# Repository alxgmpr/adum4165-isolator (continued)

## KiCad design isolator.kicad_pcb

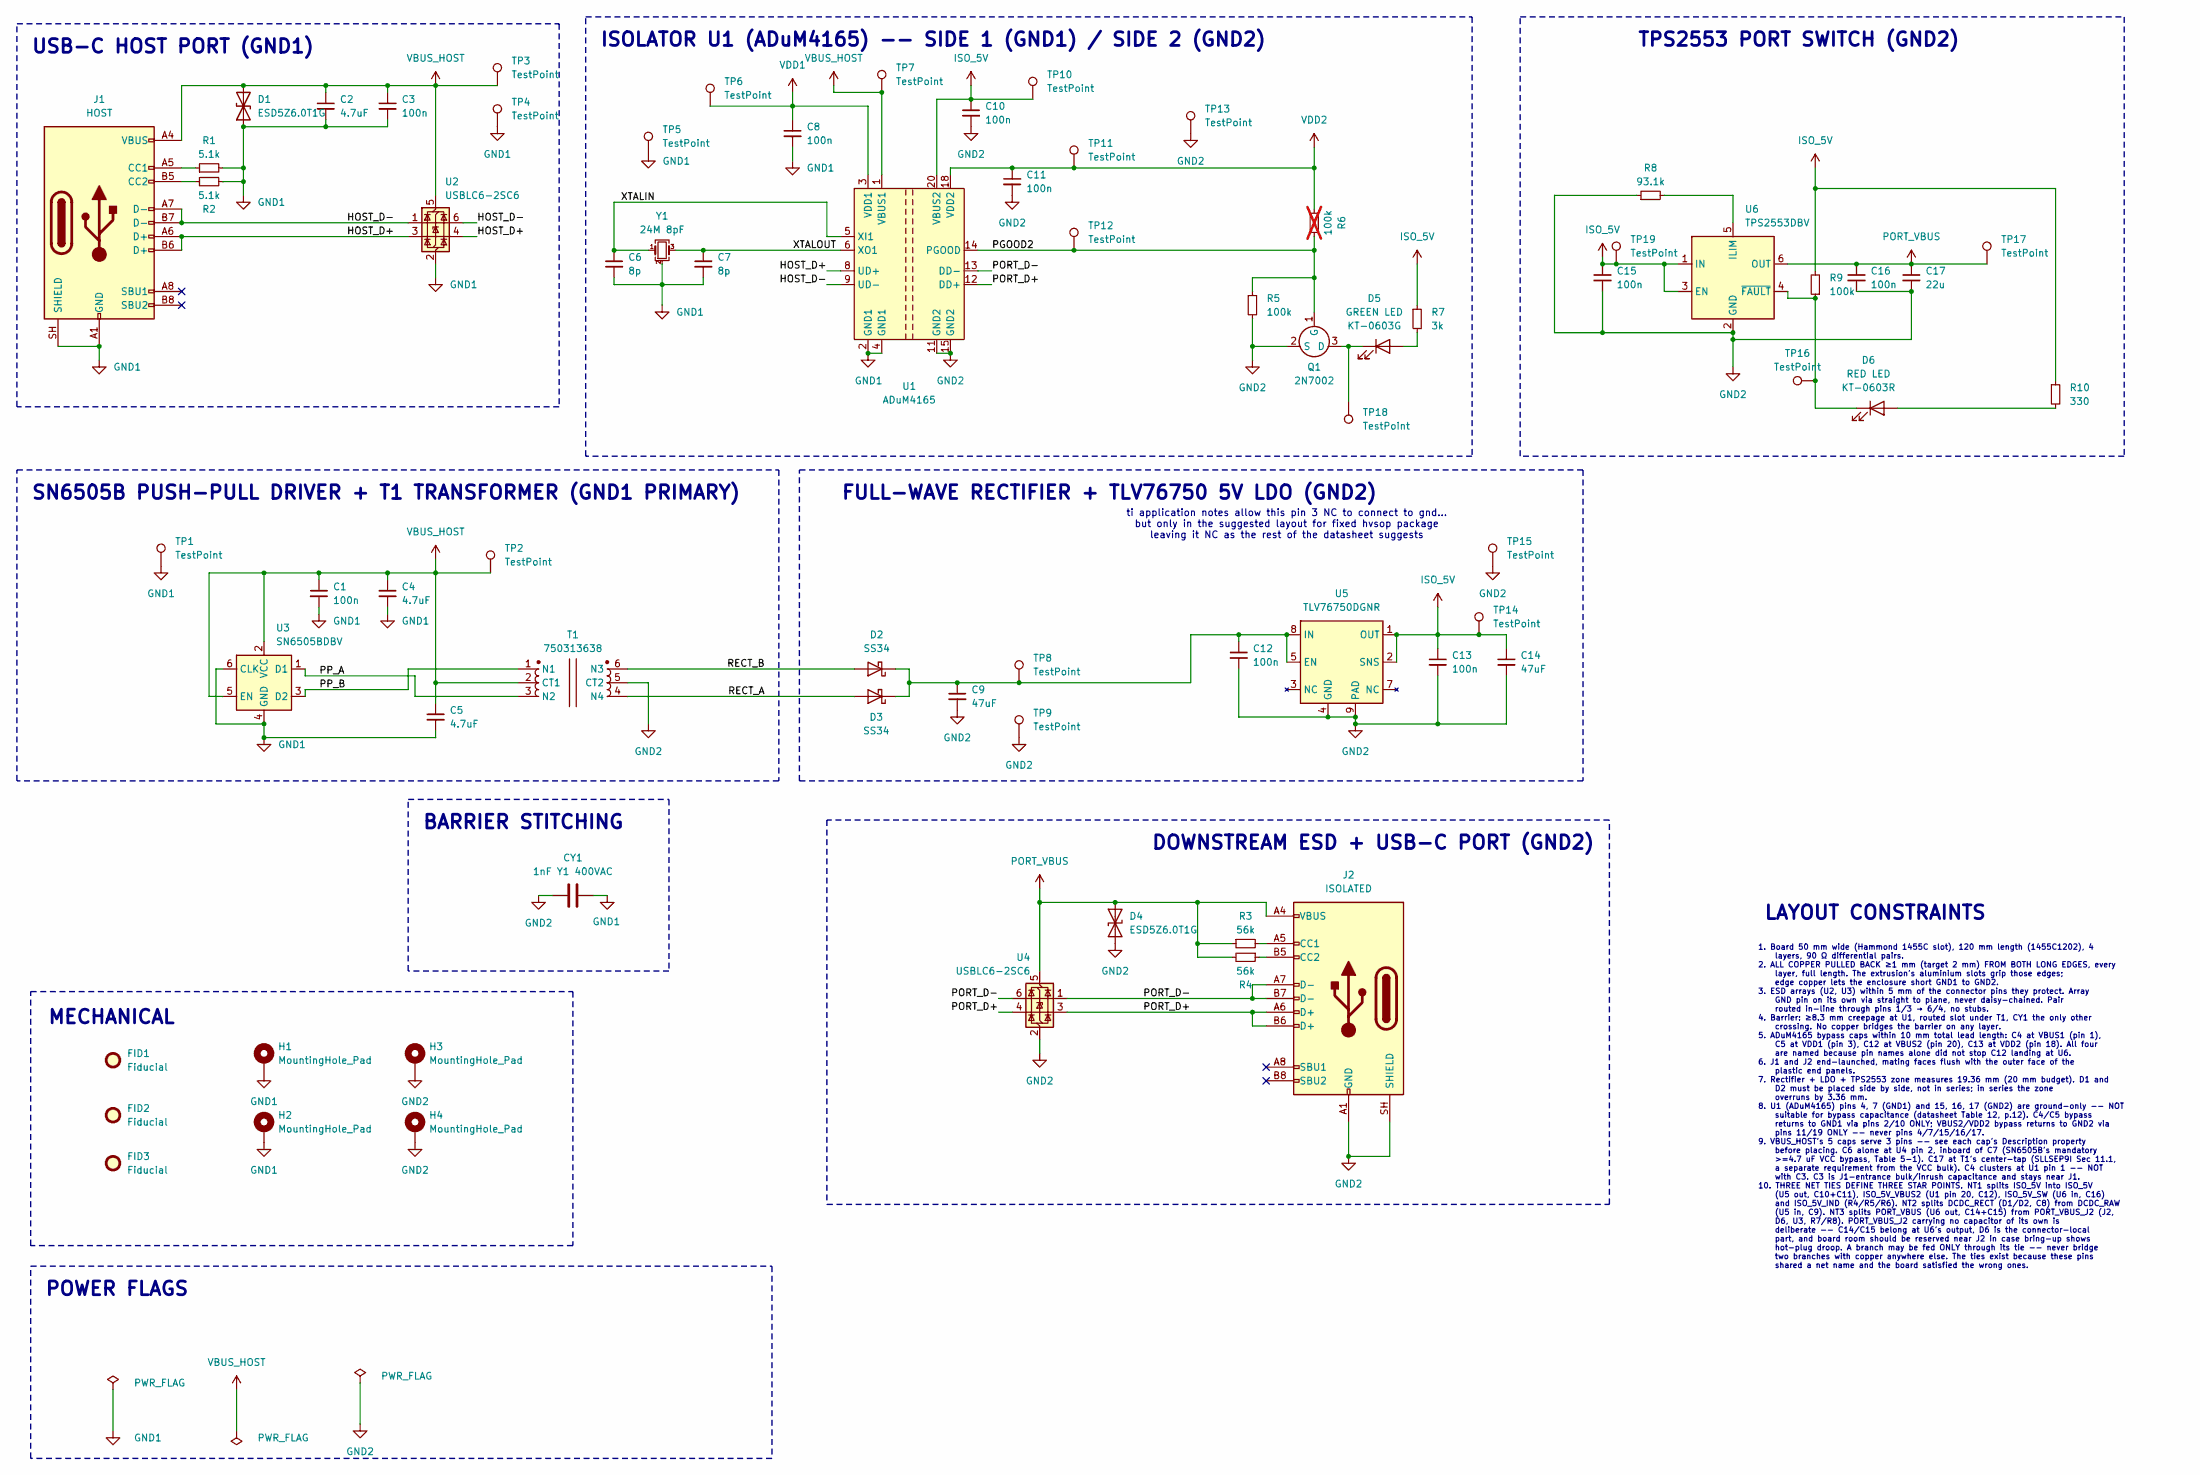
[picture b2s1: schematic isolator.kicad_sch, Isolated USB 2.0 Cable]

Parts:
C1: 100n; C_0805_2012Metric; Tolerance ±10%; MPN CC0805KRX7R9BB104; LCSC C49678
C2, C4, C5: 4.7uF; C_0805_2012Metric; MPN GRM21BR71E475KA73L; LCSC C1779
C3, C8, C10, C11, C12, C13, C15, C16: 100n; C_0603_1608Metric; Tolerance ±10%; MPN CC0603KRX7R9BB104; LCSC C14663
C6, C7: 8p; C_0603_1608Metric; Tolerance ±0.25pF; MPN CC0603CRNPO9BN8R0; LCSC C327316
C9, C14: 47uF; C_1210_3225Metric; MPN TMK325ABJ476MM-P; LCSC C90142
C17: 22u; C_0805_2012Metric; Tolerance ±10%; MPN GRM21BR61A226ME44L; LCSC C98190
CY1: 1nF Y1 400VAC; C_Disc_D7.0mm_W5.5mm_P14.00mm; Tolerance ±20%; MPN Q07F3Z102MA5B0S0N0; LCSC C2914611
D1, D4: ESD5Z6.0T1G; D_SOD-523; MPN ESD5Z6.0T1G; LCSC C82323
D2, D3: SS34; D_SMA; MPN SS34; LCSC C8678
D5: GREEN LED; LED_0603_1608Metric; MPN KT-0603G; LCSC C12624
D6: RED LED; LED_0603_1608Metric; MPN KT-0603R; LCSC C2286
FID1, FID2, FID3: Fiducial; Fiducial_1mm_Mask2mm
H1, H2, H3, H4: MountingHole_Pad; MountingHole_3.2mm_M3_Pad_Via
J1: HOST; USB_C_Receptacle_HRO_TYPE-C-31-M-12; MPN TYPE-C-31-M-12; LCSC C165948
J2: ISOLATED; USB_C_Receptacle_HRO_TYPE-C-31-M-12; MPN TYPE-C-31-M-12; LCSC C165948
Q1: 2N7002; SOT-23; MPN 2N7002LT1G; LCSC C8545
R1, R2: 5.1k; R_0603_1608Metric; Tolerance ±1%; MPN RC0603FR-075K1L; LCSC C23186
R3, R4: 56k; R_0603_1608Metric; Tolerance ±1%; MPN RC0603FR-0756KL; LCSC C23206
R5, R9: 100k; R_0603_1608Metric; Tolerance ±1%; MPN RC0603FR-07100KL; LCSC C25803
R6: 100k; R_0603_1608Metric; Tolerance ±1%; MPN RC0603FR-07100KL; LCSC C14675; not fitted
R7: 3k; R_0603_1608Metric; Tolerance ±1%; MPN RC0603FR-073KL; LCSC C4211
R8: 93.1k; R_0603_1608Metric; Tolerance ±1%; MPN RC0603FR-0793K1L; LCSC C273780
R10: 330; R_0603_1608Metric; Tolerance ±1%; MPN RC0603FR-07330RL; LCSC C23138
T1: 750313638; WE_750313638; MPN 750313638
TP1, TP2, TP3, TP4, TP5, TP6, TP7, TP8, TP9, TP10, TP11, TP12, TP13, TP14, TP15, TP16, TP17, TP18, TP19: TestPoint; TestPoint_Pad_D1.0mm
U1: ADuM4165; ADI_SOIC_IC_20_RI-20-1; MPN ADUM4165BRIZ
U2, U4: USBLC6-2SC6; SOT-23-6; MPN USBLC6-2SC6; LCSC C2687116
U3: SN6505BDBV; SOT-23-6; MPN SN6505BDBVR; LCSC C74518
U5: TLV76750DGNR; HVSSOP-8-1EP_3x3mm_P0.65mm_EP1.57x1.89mm; MPN TLV76750DGNR; LCSC C3752807
U6: TPS2553DBV; SOT-23-6; MPN TPS2553DBVR; LCSC C55266
Y1: 24M 8pF; Crystal_SMD_3225-4Pin_3.2x2.5mm; Tolerance ±30ppm; MPN SX3B24.000F0810F30; LCSC C2901675

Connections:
/HOST_D+: J1.A6 (D+), J1.B6 (D+), U1.8 (UD+), U2.3 (I/O2), U2.4 (I/O2)
/HOST_D-: J1.A7 (D-), J1.B7 (D-), U1.9 (UD-), U2.1 (I/O1), U2.6 (I/O1)
/PGOOD2: Q1.1 (G), R5.1, R6.2, TP12.1 (1_1), U1.14 (PGOOD)
/PORT_D+: J2.A6 (D+), J2.B6 (D+), U1.12 (DD+), U4.3 (I/O2), U4.4 (I/O2)
/PORT_D-: J2.A7 (D-), J2.B7 (D-), U1.13 (DD-), U4.1 (I/O1), U4.6 (I/O1)
/PP_A: T1.3 (N2), U3.1 (D1)
/PP_B: T1.1 (N1), U3.3 (D2)
/RECT_A: D3.2 (A), T1.4 (N4)
/RECT_B: D2.2 (A), T1.6 (N3)
/XTALIN: C6.1, U1.5 (XI1), Y1.1
/XTALOUT: C7.1, U1.6 (XO1), Y1.3
GND1: C1.2, C2.2, C3.2, C4.2, C5.2, C6.2, C7.2, C8.2, CY1.2, D1.1 (A1), H1.1 (1_1), H2.1 (1_1), J1.A1 (GND), J1.A12 (GND), J1.B1 (GND), J1.B12 (GND), J1.SH (SHIELD), R1.2, R2.2, TP1.1 (1_1), TP4.1 (1_1), TP5.1 (1_1), U1.2 (GND1), U1.4 (GND1), U1.7 (GND1), U1.10 (GND1), U2.2 (GND), U3.4 (GND), U3.6 (CLK), Y1.2 (G), Y1.4 (G)
GND2: C9.2, C10.2, C11.2, C12.2, C13.2, C14.2, C15.2, C16.2, C17.2, CY1.1, D4.2 (A2), H3.1 (1_1), H4.1 (1_1), J2.A1 (GND), J2.A12 (GND), J2.B1 (GND), J2.B12 (GND), J2.SH (SHIELD), Q1.2 (S), R5.2, R8.1, T1.5 (CT2), TP9.1 (1_1), TP13.1 (1_1), TP15.1 (1_1), U1.11 (GND2), U1.15 (GND2), U1.16 (GND2), U1.17 (GND2), U1.19 (GND2), U4.2 (GND), U5.4 (GND), U5.6 (GND), U5.9 (PAD), U6.2 (GND)
ISO_5V: C10.1, C13.1, C14.1, C15.1, R7.1, R9.2, R10.1, TP10.1 (1_1), TP14.1 (1_1), TP19.1 (1_1), U1.20 (VBUS2), U5.1 (OUT), U5.2 (SNS), U6.1 (IN), U6.3 (EN)
unnamed: C9.1, C12.1, D2.1 (K), D3.1 (K), TP8.1 (1_1), U5.5 (EN), U5.8 (IN)
unnamed: D5.2 (A), R7.2
unnamed: D5.1 (K), Q1.3 (D), TP18.1 (1_1)
unnamed: D6.2 (A), R10.2
unnamed: D6.1 (K), R9.1, TP16.1 (1_1), U6.4 (~FAULT)
unnamed: J1.A5 (CC1), R1.1
unnamed: J1.B5 (CC2), R2.1
unnamed: J2.A5 (CC1), R3.2
unnamed: J2.B5 (CC2), R4.1
unnamed: R8.2, U6.5 (ILIM)
PORT_VBUS: C16.1, C17.1, D4.1 (A1), J2.A4 (VBUS), J2.A9 (VBUS), J2.B4 (VBUS), J2.B9 (VBUS), R3.1, R4.2, TP17.1 (1_1), U4.5 (VBUS), U6.6 (OUT)
VBUS_HOST: C1.1, C2.1, C3.1, C4.1, C5.1, D1.2 (A2), J1.A4 (VBUS), J1.A9 (VBUS), J1.B4 (VBUS), J1.B9 (VBUS), T1.2 (CT1), TP2.1 (1_1), TP3.1 (1_1), TP7.1 (1_1), U1.1 (VBUS1), U2.5 (VBUS), U3.2 (VCC), U3.5 (EN)
VDD1: C8.1, TP6.1 (1_1), U1.3 (VDD1)
VDD2: C11.1, R6.1, TP11.1 (1_1), U1.18 (VDD2)

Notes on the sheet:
1. Board 50 mm wide (Hammond 1455C slot), 120 mm length (1455C1202), 4 layers, 90 Ω differential pairs. 2. ALL COPPER PULLED BACK ≥1 mm (target 2 mm) FROM BOTH LONG EDGES, every layer, full length. The extrusion's aluminium slots grip those edges; edge copper lets the enclosure short GND1 to GND2. 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
BARRIER STITCHING
ISOLATOR U1 (ADuM4165) -- SIDE 1 (GND1) / SIDE 2 (GND2)
USB-C HOST PORT (GND1)
MECHANICAL
DOWNSTREAM ESD + USB-C PORT (GND2)
POWER FLAGS
ti application notes allow this pin 3 NC to connect to gnd... but only in the suggested layout for fixed hvsop package leaving it NC as the rest of the datasheet suggests
LAYOUT CONSTRAINTS
SN6505B PUSH-PULL DRIVER + T1 TRANSFORMER (GND1 PRIMARY)
TPS2553 PORT SWITCH (GND2)
FULL-WAVE RECTIFIER + TLV76750 5V LDO (GND2)

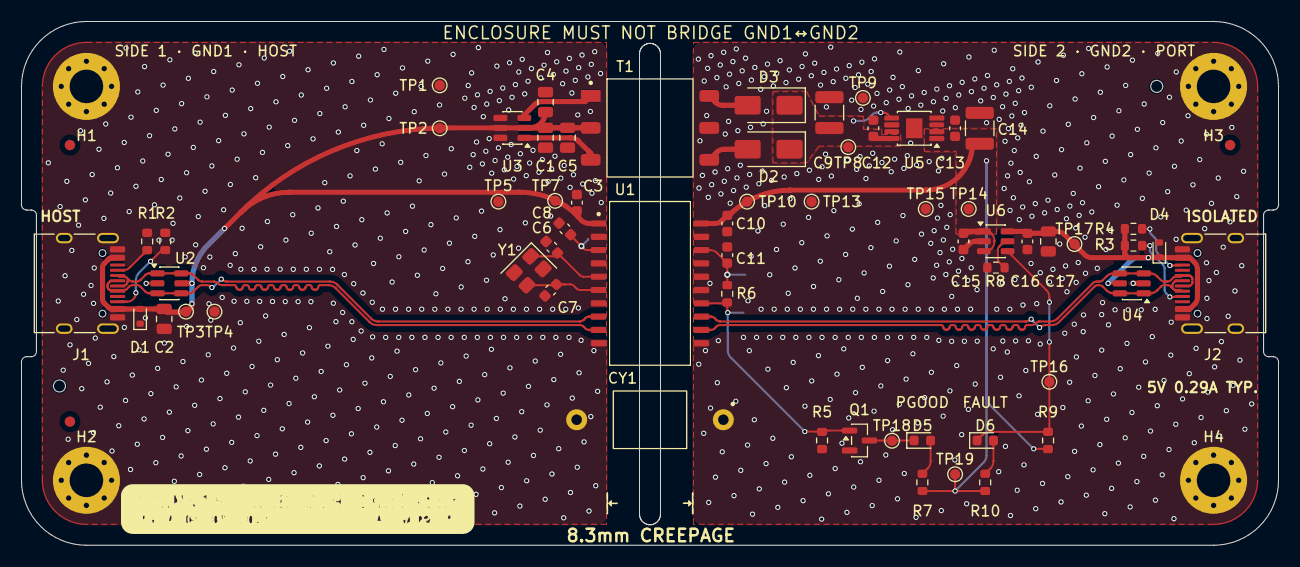
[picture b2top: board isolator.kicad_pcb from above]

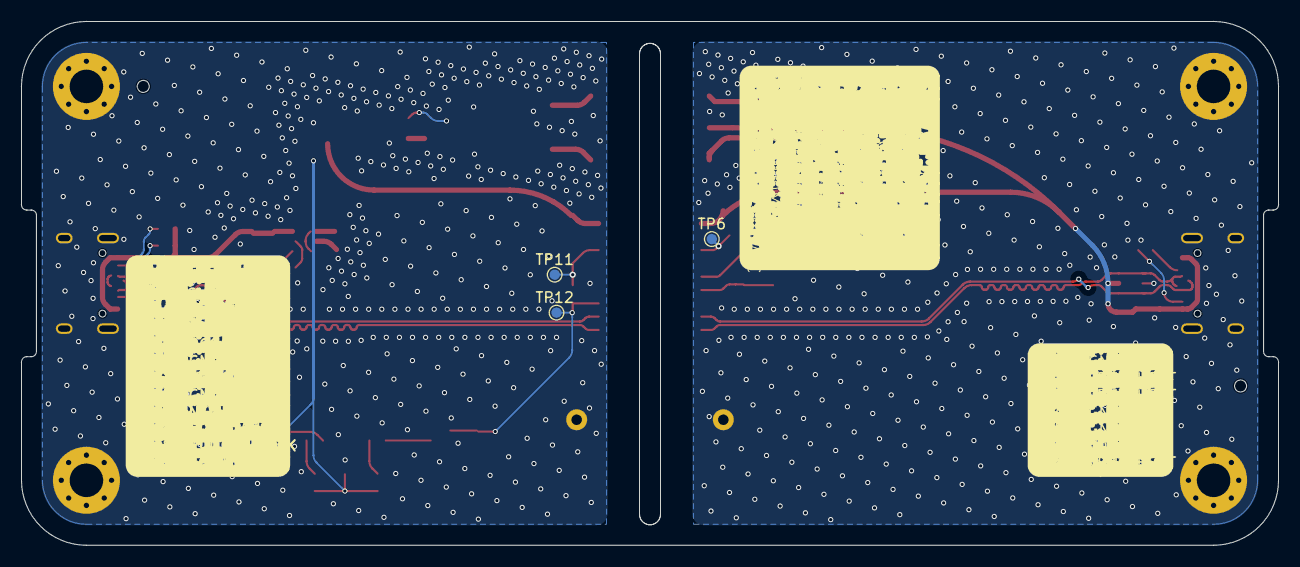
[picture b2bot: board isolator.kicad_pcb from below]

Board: 4 copper layers, 120.0 x 50.0 mm, 73 parts (3 on the bottom side), 28 nets.

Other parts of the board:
TH1, TH2: ToolingHole_1.152mm

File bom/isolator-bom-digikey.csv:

Reference,Qty/Board,Value,Footprint,Original MPN,DigiKey PN,DigiKey MPN,Manufacturer,Match,DK Stock,Unit @ 5bd,Ext 5 bd,Unit @ 10bd,Ext 10 bd,Unit @ 25bd,Ext 25 bd,Notes
C1,1,100n,C_0805,CC0805KRX7R9BB104,311-1140-1-ND,CC0805KRX7R9BB104,YAGEO,exact,2079010,0.14000,0.70,0.07600,0.76,0.07600,1.90,
"C2,C4,C5",3,4.7uF,C_0805,GRM21BR71E475KA73L,587-2990-1-ND,TMK212AB7475KG-T,Taiyo Yuden,SUB,798508,0.14700,2.21,0.14700,4.41,0.10560,7.92,Original Murata part is OBSOLETE at DigiKey. Taiyo Yuden 4.7uF 25V X7R 0805.
"C3,C8,C10,C11,C12,C13,C15,C16",8,100n,C_0603,CC0603KRX7R9BB104,1276-6854-1-ND,CL10B104KB8WPNC,Samsung Electro-Mechanics,SUB,195619,0.05500,2.20,0.03780,3.02,0.03250,6.50,Exact Yageo part is 0 stock at DigiKey (Mouser 603-CC603KRX7R9BB104 has 51M). Samsung 100nF 50V X7R 10%.
"C6,C7",2,8p,C_0603,CC0603CRNPO9BN8R0,311-3864-1-ND,CC0603CRNPO9BN8R0,YAGEO,exact,5962,0.09300,0.93,0.09300,1.86,0.06460,3.23,
"C9,C14",2,47uF,C_1210,TMK325ABJ476MM-P,587-5479-1-ND,TMK325ABJ476MM-P,Taiyo Yuden,exact,34325,0.77900,7.79,0.77900,15.58,0.61040,30.52,
C17,1,22u,C_0805,GRM21BR61A226ME44L,445-7663-1-ND,C2012X5R1A226M085AC,TDK,SUB,123281,0.32000,1.60,0.18800,1.88,0.18800,4.70,Exact Murata part 0 stock at DigiKey. TDK 22uF 10V X5R 0805.
CY1,1,1nF Y1 400VAC,Disc D7.0 P14.00,Q07F3Z102MA5B0S0N0,490-DE1E3RA102MJ4BH01F-ND,DE1E3RA102MJ4BH01F,Murata Electronics,-> MOUSER,5906,0.83000,4.15,0.52600,5.26,0.52600,13.15,"*** Buy from Mouser 81-DE1E3A102MJ4BH01F (2072 stk, $0.83/1, $0.405/10) -- cheaper than DigiKey at qty 10. Murata X1/Y1 400VAC 1nF, 7.00mm dia (matches), 10mm lead spacing vs the 14mm footprint pitch, so leads splay on assembly. Y1 rating is mandatory. Through-hole -- JLC will not place it."
"D1,D4",2,ESD5Z6.0T1G,SOD-523,ESD5Z6.0T1G,ESD5Z6.0T1GOSCT-ND,ESD5Z6.0T1G,onsemi,exact,762,0.13400,1.34,0.13400,2.68,0.09540,4.77,"Schematic now specifies this part (was T6V0S5A-7, which is dry at DigiKey and Mouser and down to 51 pcs at JLC). onsemi uni TVS 6Vrwm / 20.5Vc. JLC C82323 has 11798 -- both BOMs now agree."
"D2,D3",2,SS34,D_SMA,SS34,SS34FSCT-ND,SS34,onsemi,exact,67674,0.63100,6.31,0.63100,12.62,0.46480,23.24,Cheaper on Mouser: 821-SS34 (Taiwan Semi) $0.79/1 vs $1.01.
D5,1,GREEN LED,LED_0603,KT-0603G,160-1435-1-ND,LTST-C190KGKT,Lite-On Inc.,SUB,1826340,0.15000,0.75,0.10400,1.04,0.10400,2.60,DigiKey does not carry KENTO. Lite-On LTST-C190KGKT green 0603. Verify Vf/If vs R10=330.
D6,1,RED LED,LED_0603,KT-0603R,160-1436-1-ND,LTST-C190KRKT,Lite-On Inc.,SUB,869864,0.14000,0.70,0.09800,0.98,0.09800,2.45,DigiKey does not carry KENTO. Lite-On LTST-C190KRKT red 0603.
"J1,J2",2,USB-C 16P,HRO TYPE-C-31-M-12,TYPE-C-31-M-12,2073-USB4105-GF-ACT-ND,USB4105-GF-A,GCT,SUB-CHECK FP,96856,0.67600,6.76,0.67600,13.52,0.60340,30.17,"DigiKey does not carry HRO. GCT USB4105-GF-A is the closest land pattern: shell slots identical (+/-4.32mm, y -3.105/+1.075 vs HRO -3.13/+1.05), but the SMD contact row sits 0.34mm closer to the shell (dy 0.575 vs 0.915). ~80% pad overlap -- change the footprint to USB_C_Receptacle_GCT_USB4105-xx-A_16P_TopMnt_Horizontal before ordering."
Q1,1,2N7002,SOT-23,2N7002LT1G,1727-8643-1-ND,2N7002NXAKR,Nexperia USA Inc.,SUB,218440,0.14000,0.70,0.08600,0.86,0.08600,2.15,"Exact onsemi part 0 stock at DigiKey (Mouser 863-2N7002LT1G has 40k). Nexperia 2N7002NXAKR, 60V / 190mA vs 115mA -- fine for the PGOOD buffer."
"R1,R2",2,5.1k,R_0603,RC0603FR-075K1L,311-5.10KHRCT-ND,RC0603FR-075K1L,YAGEO,exact,634744,0.02700,0.27,0.02700,0.54,0.01580,0.79,
"R3,R4",2,56k,R_0603,RC0603FR-0756KL,RMCF0603FT56K0CT-ND,RMCF0603FT56K0,Stackpole Electronics Inc,SUB,111213,0.02100,0.21,0.02100,0.42,0.01200,0.60,Exact Yageo part 0 stock at DigiKey. Stackpole 56k 1% 0603.
"R5,R9",2,100k,R_0603,RC0603FR-07100KL,311-100KHRCT-ND,RC0603FR-07100KL,YAGEO,exact,2174279,0.02500,0.25,0.02500,0.50,0.01500,0.75,
R7,1,3k,R_0603,RC0603FR-073KL,311-3.00KHRCT-ND,RC0603FR-073KL,YAGEO,exact,9163,0.10000,0.50,0.02500,0.25,0.01880,0.47,"Value changed 3.01k -> 3k (LED series resistor, ~1mA -- 0.3% shift is immaterial). Buys a JLC Basic part (C4211), removing one extended-part fee."
R8,1,93.1k,R_0603,RC0603FR-0793K1L,311-93.1KHRCT-ND,RC0603FR-0793K1L,YAGEO,exact,26511,0.10000,0.50,0.02500,0.25,0.01880,0.47,
R10,1,330,R_0603,RC0603FR-07330RL,311-330HRCT-ND,RC0603FR-07330RL,YAGEO,exact,1021515,0.10000,0.50,0.02500,0.25,0.01880,0.47,
T1,1,750313638,WE_750313638,750313638,1297-1105-1-ND,750313638,Würth Elektronik,exact / NO STOCK,0,3.60000,18.00,3.25500,32.55,3.12520,78.13,"*** 0 stock at DigiKey. Mouser 710-750313638 has 4624 in stock, $4.07/1 $3.81/10 $3.52/50. Order T1 from Mouser."
U1,1,ADuM4165,SOIC-20 RI-20-1,ADUM4165BRIZ,505-ADUM4165BRIZ-ND,ADUM4165BRIZ,Analog Devices Inc.,exact / NO STOCK,0,18.09000,90.45,14.37900,143.79,14.37900,359.48,"*** 0 stock at DigiKey (all variants incl. -RL). Mouser 584-ADUM4165BRIZ shows 1814 ON ORDER, 301-day lead, $18.24/1. This is the schedule driver -- check Arrow/Avnet/Newark or ADI direct."
"U2,U4",2,USBLC6-2SC6,SOT-23-6,USBLC6-2SC6,497-5235-1-ND,USBLC6-2SC6,STMicroelectronics,exact,56982,0.34900,3.49,0.34900,6.98,0.25260,12.63,
U3,1,SN6505BDBV,SOT-23-6,SN6505BDBVR,296-47311-1-ND,SN6505BDBVR,Texas Instruments,exact,11852,2.23000,11.15,1.65300,16.53,1.50760,37.69,
U5,1,TLV76750DGNR,HVSSOP-8,TLV76750DGNR,296-TLV76750DGNRCT-ND,TLV76750DGNR,Texas Instruments,exact,1314,1.05000,5.25,0.75700,7.57,0.68360,17.09,Only 1314 in stock -- thin. Mouser has it too.
U6,1,TPS2553DBV,SOT-23-6,TPS2553DBVR,296-23990-1-ND,TPS2553DBVT,Texas Instruments,exact-alt,6693,1.36000,6.80,0.98500,9.85,0.89120,22.28,"Same silicon: TPS2553DBVT is the 250-pc reel, DBVR (3000-pc) is 0 stock at DigiKey."
Y1,1,24M 8pF,Crystal 3225-4Pin,SX3B24.000F0810F30,478-CX3225FB24000D0FZZH1CT-ND,CX3225FB24000D0FZZH1,KYOCERA AVX,SUB,8500,0.34000,1.70,0.29700,2.97,0.28040,7.01,"DigiKey does not carry SCTF. Kyocera AVX 24MHz, 3.2x2.5mm, 8pF load (matches C6/C7), +/-10ppm tol / +/-20ppm stab, 40 ohm ESR -- tighter than the original +/-30ppm."
TP1-TP19,19,TestPoint,Pad D1.0mm,,,,,n/a,,,,,,,,"Bare pads, no part to order."

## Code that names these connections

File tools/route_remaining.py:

"""Close the last unconnected items the autorouter left on the isolated side.

Every proposed segment is validated against existing pads, vias and tracks on the
same layer BEFORE it is added, and the script refuses to add a colliding one.
Placing waypoints without that check is what produced seven shorts on the first
attempt.

Geometry that drove the waypoints:

/DCDC_RAW -- U5's supply pins 5 and 8 are both in the RIGHT column (x=89.150,
  y=11.975 and 10.025) with pins 6 and 7 between them, so they cannot be joined
  by a vertical: the link has to go around the package past x=90.175. Freerouting
  also stopped 1 um short of C8.1, subdividing its approach 78.500, 78.513,
  78.519, 78.522, 78.523, 78.524 and never reaching 78.525.

/ISO_5V -- U5's output pins 1 and 2 are adjacent in the LEFT column so they join
  directly, but the run onward to C10 must clear pin 3 at (84.850, 11.325) by
  leaving to the left of the package first.

/PORT_VBUS -- D6.1 and U3.5 are both boxed in between the two halves of the
  differential pair (D+ at y=24.050, D- at y=25.950, both spanning x 102..109.3).
  Each reaches the existing B.Cu PORT_VBUS spine at y=24.091 through a via placed
  in a verified gap rather than by crossing the pair.
"""
import sys, math, pcbnew

BOARD = sys.argv[1]
b = pcbnew.LoadBoard(BOARD)
IU, MM = pcbnew.FromMM, pcbnew.ToMM
CLEAR = 0.16

FCU, BCU = pcbnew.F_Cu, pcbnew.B_Cu
LAYER = {'F': FCU, 'B': BCU}


def seg_dist(px, py, x1, y1, x2, y2):
    dx, dy = x2 - x1, y2 - y1
    if dx == 0 and dy == 0:
        return math.hypot(px - x1, py - y1)
    t = max(0.0, min(1.0, ((px - x1) * dx + (py - y1) * dy) / (dx * dx + dy * dy)))
    return math.hypot(px - (x1 + t * dx), py - (y1 + t * dy))


def ss_dist(a1, a2, c1, c2):
    return min(seg_dist(*a1, *c1, *c2), seg_dist(*a2, *c1, *c2),
               seg_dist(*c1, *a1, *a2), seg_dist(*c2, *a1, *a2))


def snapshot():
    pads, vias, segs = [], [], []
    for f in b.GetFootprints():
        for p in f.Pads():
            bb = p.GetBoundingBox()
            layers = [l for l in (FCU, BCU) if p.IsOnLayer(l)]
            pads.append((MM(bb.GetLeft()), MM(bb.GetTop()), MM(bb.GetRight()),
                         MM(bb.GetBottom()), p.GetNetname(), layers))
    for t in b.GetTracks():
        if t.GetClass() == 'PCB_VIA':
            p = t.GetPosition()
            vias.append((MM(p.x), MM(p.y), MM(t.GetWidth()) / 2, t.GetNetname()))
        else:
            s, e = t.GetStart(), t.GetEnd()
            segs.append((MM(s.x), MM(s.y), MM(e.x), MM(e.y),
                         MM(t.GetWidth()) / 2, t.GetNetname(), t.GetLayer()))
    return pads, vias, segs


def collides(p1, p2, w, netname, lid):
    pads, vias, segs = snapshot()
    hw = w / 2
    for x0, y0, x1, y1, n, layers in pads:
        if n == netname or lid not in layers:
            continue
        for e in ((x0, y0, x1, y0), (x1, y0, x1, y1), (x1, y1, x0, y1), (x0, y1, x0, y0)):
            if ss_dist(p1, p2, (e[0], e[1]), (e[2], e[3])) < hw + CLEAR:
                return "pad %s" % n
    for vx, vy, vr, n in vias:
        if n == netname:
            continue
        if seg_dist(vx, vy, p1[0], p1[1], p2[0], p2[1]) < hw + vr + CLEAR:
            return "via %s" % n
    for x1, y1, x2, y2, ohw, n, l in segs:
        if n == netname or l != lid:
            continue
        if ss_dist(p1, p2, (x1, y1), (x2, y2)) < hw + ohw + CLEAR:
            return "track %s" % n
    return None


ROUTES = [
    # --- DCDC_RAW trunk: C8.1 down, under C8/U5, to the left of the package ---
    ('/DCDC_RAW', 'F', [(78.525, 11.000), (78.525, 13.400), (83.000, 13.400)], 0.5),
    # C9 input cap, now beside the input pins
    ('/DCDC_RAW', 'F', [(78.525, 11.000), (78.525, 7.000), (80.225, 7.000)], 0.5),

    # --- PORT_VBUS: U3.5 is boxed in on F.Cu between pair pins 4 and 6, and every
    # F.Cu escape crosses one half of the pair, so it drops to B.Cu in its own pad.
    ('/PORT_VBUS', 'B', [(108.638, 25.000), (108.901, 24.700), (108.901, 24.091)], 0.4),
]
VIAS = [(108.638, 25.000, '/PORT_VBUS')]

# Fine-pitch approaches. U5's pads are 0.5 mm tall with 0.150 mm between
# neighbours, so a 0.5 mm trunk cannot enter a pin: these neck down to 0.25 mm.
# The trunk x is searched rather than hard-coded because GND stitching vias sit
# in the channel to the left of the package.
APPROACHES = [
    ('/DCDC_RAW', (83.000, 13.400), 11.975, 84.125, 0.25),   # -> U5.8
    ('/DCDC_RAW', (83.000, 13.400), 10.025, 84.125, 0.25),   # -> U5.5
]
LINKS = [
    ('/ISO_5V', (89.150, 11.975), (89.150, 11.325), 0.25),   # U5.1 - U5.2, adjacent pins
]

added = rejected = 0
for net, layer, pts, w in ROUTES:
    lid = LAYER[layer]
    ni = b.FindNet(net)
    for p1, p2 in zip(pts, pts[1:]):
        why = collides(p1, p2, w, net, lid)
        if why:
            print("  REJECT %-12s %s.Cu (%.3f,%.3f)->(%.3f,%.3f): hits %s"
                  % (net, layer, p1[0], p1[1], p2[0], p2[1], why))
            rejected += 1
            continue
        t = pcbnew.PCB_TRACK(b)
        t.SetStart(pcbnew.VECTOR2I(IU(p1[0]), IU(p1[1])))
        t.SetEnd(pcbnew.VECTOR2I(IU(p2[0]), IU(p2[1])))
        t.SetWidth(IU(w)); t.SetLayer(lid); t.SetNetCode(ni.GetNetCode())
        b.Add(t)
        added += 1

for x, y, net in VIAS:
    v = pcbnew.PCB_VIA(b)
    v.SetPosition(pcbnew.VECTOR2I(IU(x), IU(y)))
    v.SetWidth(IU(0.5)); v.SetDrill(IU(0.3))
    v.SetViaType(pcbnew.VIATYPE_THROUGH)
    v.SetLayerPair(FCU, BCU)
    v.SetNetCode(b.FindNet(net).GetNetCode())
    b.Add(v)

for net, trunk, ypin, xpin, w in APPROACHES:
    ni = b.FindNet(net)
    done = False
    for xv in (trunk[0], trunk[0] - 0.3, trunk[0] - 0.6, trunk[0] + 0.3, trunk[0] - 0.9):
        legs = [((trunk[0], trunk[1]), (xv, trunk[1])),
                ((xv, trunk[1]), (xv, ypin)),
                ((xv, ypin), (xpin, ypin))]
        legs = [l for l in legs if l[0] != l[1]]
        why = next((collides(a, c, w, net, FCU) for a, c in legs
                    if collides(a, c, w, net, FCU)), None)
        if why:
            continue
        for a, c in legs:
            t = pcbnew.PCB_TRACK(b)
            t.SetStart(pcbnew.VECTOR2I(IU(a[0]), IU(a[1])))
            t.SetEnd(pcbnew.VECTOR2I(IU(c[0]), IU(c[1])))
            t.SetWidth(IU(w)); t.SetLayer(FCU); t.SetNetCode(ni.GetNetCode())
            b.Add(t)
            added += 1
        print("  approach %-12s -> y=%.3f via trunk x=%.3f" % (net, ypin, xv))
        done = True
        break
    if not done:
        print("  NO CLEAR APPROACH %-12s -> y=%.3f" % (net, ypin))
        rejected += 1

for net, a, c, w in LINKS:
    ni = b.FindNet(net)
    why = collides(a, c, w, net, FCU)
    if why:
        print("  REJECT link %-12s: hits %s" % (net, why)); rejected += 1; continue
    t = pcbnew.PCB_TRACK(b)
    t.SetStart(pcbnew.VECTOR2I(IU(a[0]), IU(a[1])))
    t.SetEnd(pcbnew.VECTOR2I(IU(c[0]), IU(c[1])))
    t.SetWidth(IU(w)); t.SetLayer(FCU); t.SetNetCode(ni.GetNetCode())
    b.Add(t); added += 1
    print("  link %-12s ok" % net)

print("segments added: %d, rejected: %d" % (added, rejected))
pcbnew.ZONE_FILLER(b).Fill(b.Zones())
pcbnew.SaveBoard(BOARD, b)
print("saved")
